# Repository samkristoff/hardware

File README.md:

hardware
========

Temp HW Repo

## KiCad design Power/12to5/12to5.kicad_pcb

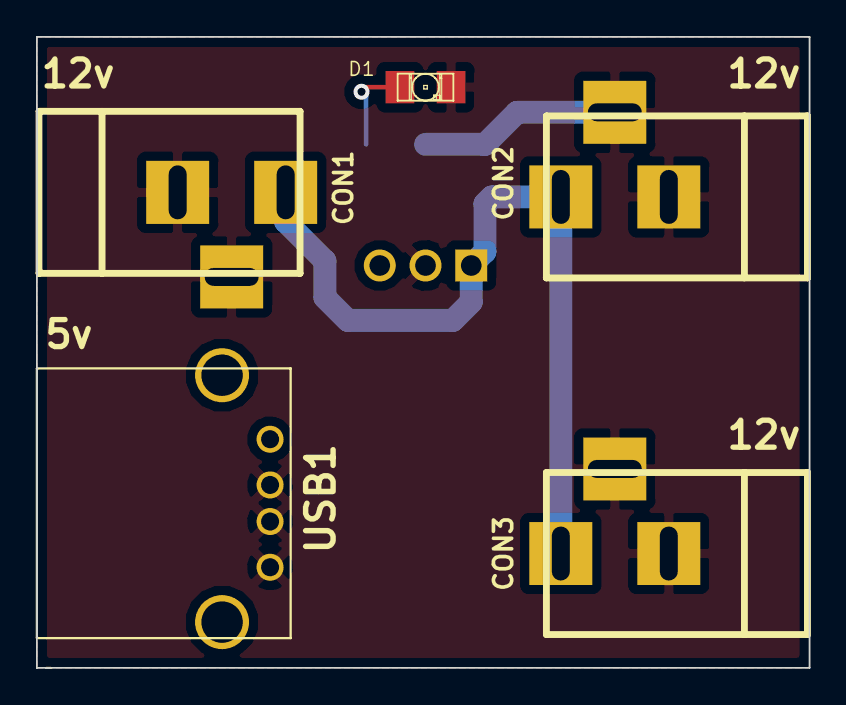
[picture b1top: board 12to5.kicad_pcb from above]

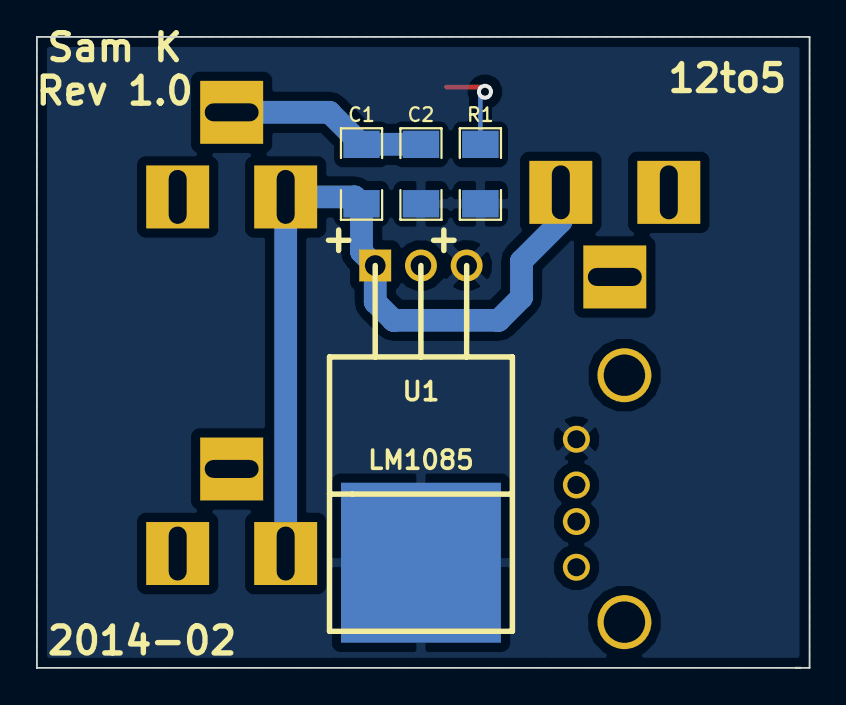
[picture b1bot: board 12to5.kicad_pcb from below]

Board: 2 copper layers, 42.9 x 35.1 mm, 9 parts (4 on the bottom side), 4 nets.

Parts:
C1: 10u; SM1206
C2: 100u; SM1206
CON1, CON2, CON3: BARREL_JACK
D1: LED; LED-1206
R1: R; SM1206
U1: LM1085; TO220
U2: USB1; USB_A

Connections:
+5V: C2.1, R1.1, U1.2, U1.4, U2.1
+12V: C1.1, CON1.1, CON2.1, CON3.1, U1.1
GND: C1.2, C2.2, CON1.2, CON1.3, CON2.2, CON2.3, CON3.2, CON3.3, D1.2, U1.3, U2.2, U2.3, U2.4
unnamed: D1.1, R1.2

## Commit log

2014-02-09 Added 12to5 schematic Added LM1085 Component Added USB_A Component
2014-02-09 Added PCB Added Gerbers Rev 1.0 Complete
2014-02-09 Updated LM1085 to be use SMD tab but throughole pins Fixed Text
